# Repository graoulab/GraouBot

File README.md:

# GraouBot
A robot to teach kids from 7 to 77

GraouBotShpere, a small spherical bot

Folder Electronic contain the electronic card KiCad's project

Folder Mecanic contain the entire bot 3mm MDF pieces in one board ready to laser cut.

Folder Program contain an Arduino librairy with samples.

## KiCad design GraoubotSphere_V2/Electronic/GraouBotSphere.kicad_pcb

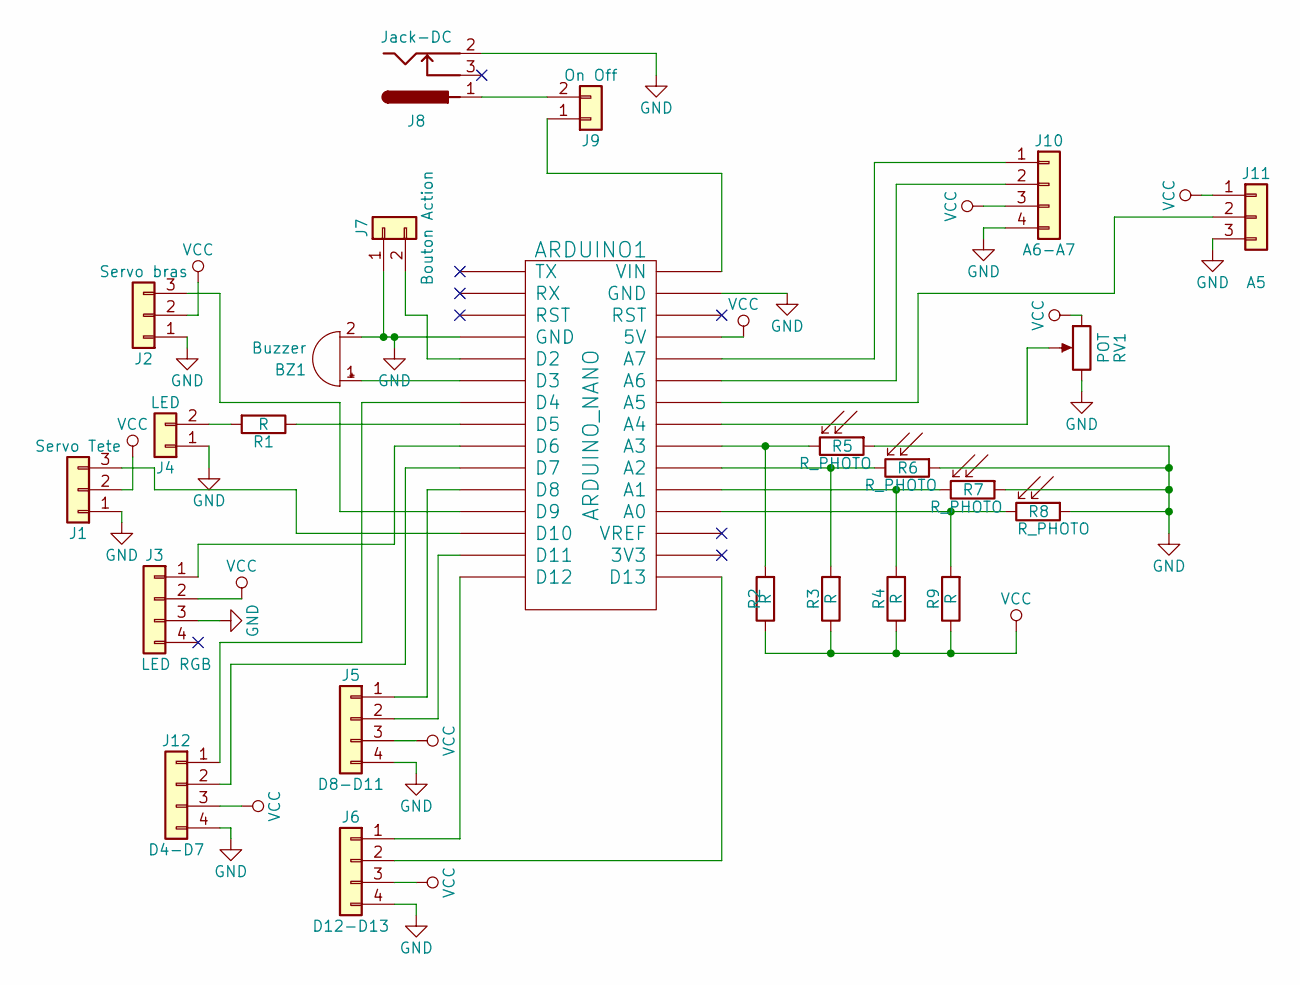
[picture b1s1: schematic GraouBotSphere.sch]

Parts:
ARDUINO1: ARDUINO_NANO; Arduino_Nano
BZ1: Buzzer; Buzzer_12x9.5RM7.6
J1: Servo Tete; Pin_Header_Straight_1x03_Pitch2.54mm
J2: Servo bras; Pin_Header_Straight_1x03_Pitch2.54mm
J3: LED RGB; Pin_Header_Straight_1x04_Pitch2.54mm
J4: LED; Pin_Header_Straight_1x02_Pitch2.54mm
J5: D8-D11; Pin_Header_Straight_1x04_Pitch2.54mm
J6: D12-D13; Pin_Header_Straight_1x04_Pitch2.54mm
J7: Bouton Action; SW_Tactile_SPST_Angled_PTS645Vx83-2LFS
J8: Jack-DC; JACK_ALIM
J9: On Off; SW_CuK_OS102011MA1QN1_SPDT_Angled
J10: A6-A7; Pin_Header_Straight_1x04_Pitch2.54mm
J11: A5; Pin_Header_Straight_1x03_Pitch2.54mm
J12: D4-D7; Pin_Header_Straight_1x04_Pitch2.54mm
R1, R2, R3, R4, R9: R; R_1206_HandSoldering
R5, R6, R7, R8: R_PHOTO; Resistor_LDR_4.9x4.2_RM2.54
RV1: POT; Potentiometer_Bourns_PTV09A-2_Vertical

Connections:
GND: ARDUINO1.4 (GND), ARDUINO1.29 (GND), BZ1.2 (+), J1.1, J2.1, J3.3, J4.1, J5.4, J6.4, J7.1, J8.2, J10.4, J11.3, J12.4, R5.1, R6.1, R7.1, R8.1, RV1.3; also elsewhere on the board
unnamed: ARDUINO1.5 (D2), J7.2
unnamed: ARDUINO1.6 (D3), BZ1.1 (-)
unnamed: ARDUINO1.7 (D4), J12.1
unnamed: ARDUINO1.8 (D5), R1.1
unnamed: ARDUINO1.9 (D6), J3.1
unnamed: ARDUINO1.10 (D7), J12.2
unnamed: ARDUINO1.11 (D8), J5.1
unnamed: ARDUINO1.12 (D9), J2.3
unnamed: ARDUINO1.13 (D10), J1.3
unnamed: ARDUINO1.14 (D11), J5.2
unnamed: ARDUINO1.15 (D12), J6.1
unnamed: ARDUINO1.16 (D13), J6.2
unnamed: ARDUINO1.19 (A0), R8.2, R9.2
unnamed: ARDUINO1.20 (A1), R4.2, R7.2
unnamed: ARDUINO1.21 (A2), R3.2, R6.2
unnamed: ARDUINO1.22 (A3), R2.2, R5.2
unnamed 17: ARDUINO1.23 (A4), RV1.2; also elsewhere on the board
unnamed: ARDUINO1.24 (A5), J11.2
unnamed: ARDUINO1.25 (A6), J10.2
unnamed: ARDUINO1.26 (A7), J10.1
unnamed: ARDUINO1.30 (VIN), J9.1
unnamed: J4.2, R1.2
unnamed: J8.1, J9.2
VCC: ARDUINO1.27 (5V), J1.2, J2.2, J3.2, J5.3, J6.3, J10.3, J11.1, J12.3, R2.1, R3.1, R4.1, R9.1, RV1.1; also elsewhere on the board

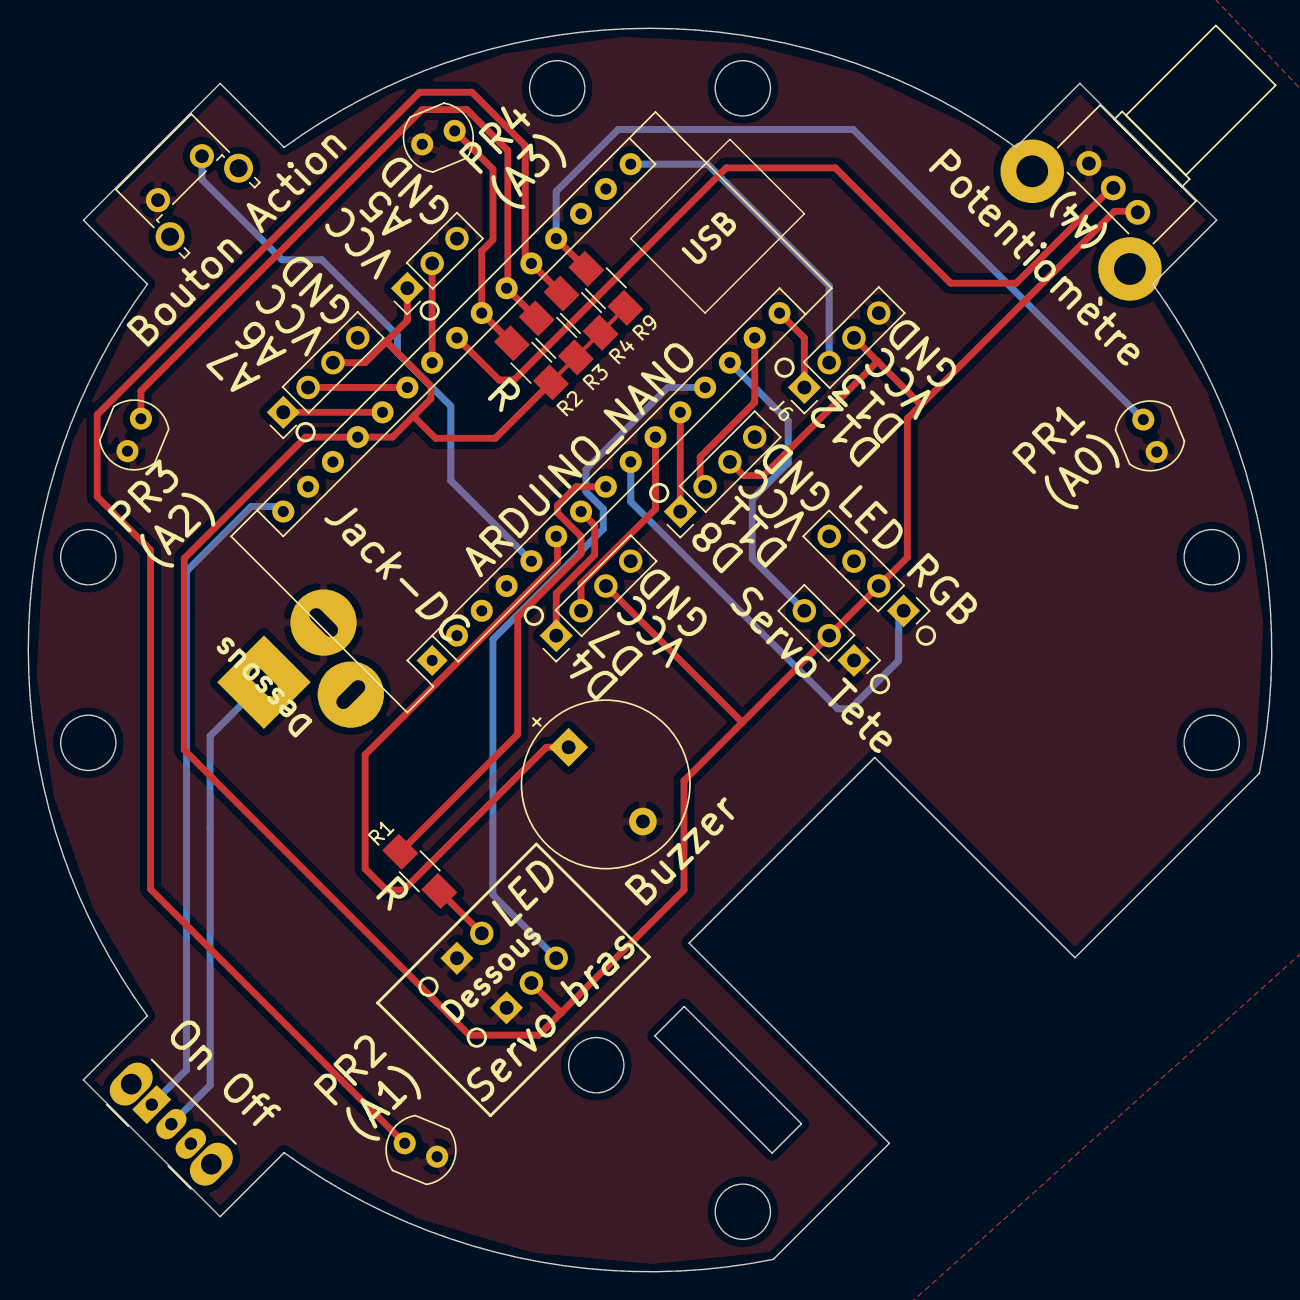
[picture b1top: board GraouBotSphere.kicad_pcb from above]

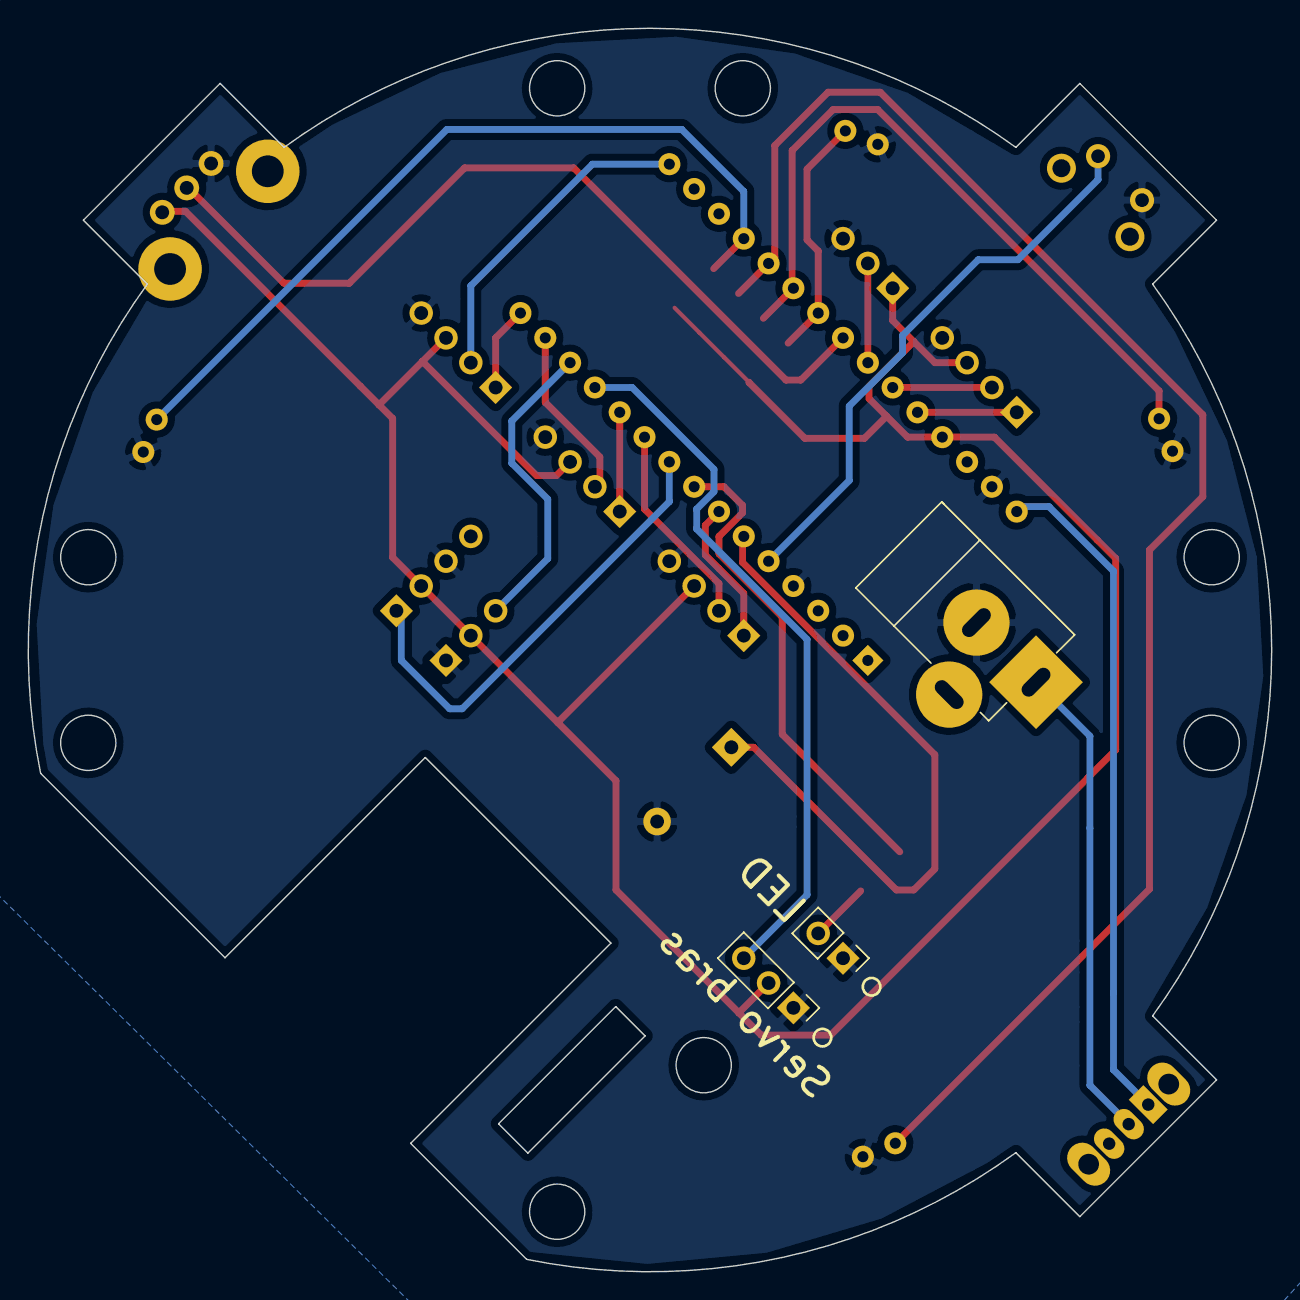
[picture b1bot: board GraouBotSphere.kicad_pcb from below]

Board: 2 copper layers, 90.0 x 90.0 mm, 24 parts (3 on the bottom side), 25 nets.

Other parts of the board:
Potentiomètre: POT; Potentiometer_Bourns_PTV09A-2_Vertical

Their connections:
GND: Potentiomètre.3; also elsewhere on the board
unnamed 17: Potentiomètre.2; also elsewhere on the board
VCC: Potentiomètre.1; also elsewhere on the board

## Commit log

2018-03-18 GraoubotSphere V2
    GraoubotSphere V2
    First comit
